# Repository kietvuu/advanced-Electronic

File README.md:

# advanced-Electronic
this is our project about H-bridge connection controlling a DC motor

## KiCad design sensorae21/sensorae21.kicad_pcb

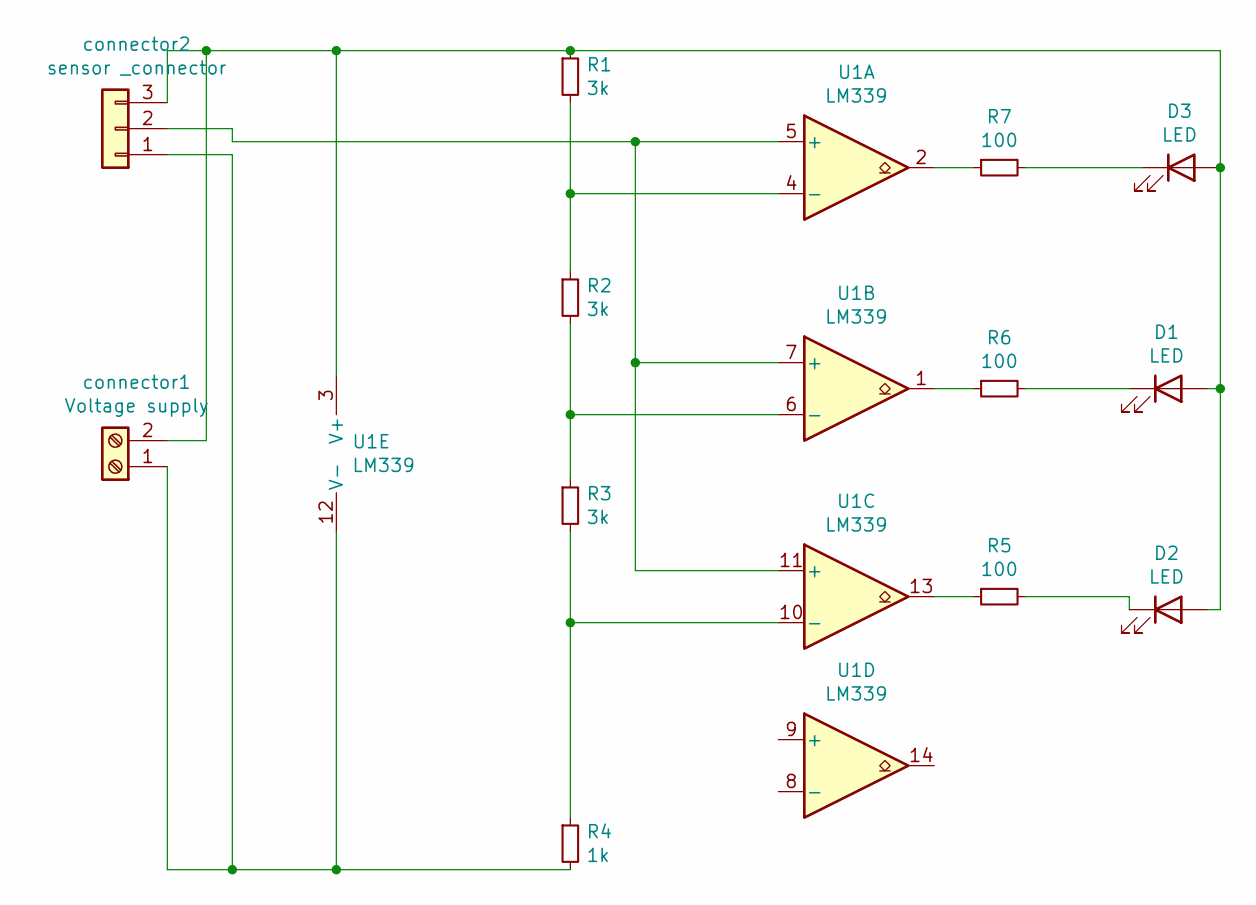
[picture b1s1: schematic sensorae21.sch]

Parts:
D1, D2, D3: LED; LED_D5.0mm
R1, R2, R3: 3k; R_Axial_DIN0309_L9.0mm_D3.2mm_P5.08mm_Vertical
R4: 1k; R_Axial_DIN0309_L9.0mm_D3.2mm_P5.08mm_Vertical
R5, R6, R7: 100; R_Axial_DIN0309_L9.0mm_D3.2mm_P5.08mm_Vertical
U1: LM339; DIP-14_W7.62mm
connector1: Voltage supply; PinSocket_1x02_P2.54mm_Vertical
connector2: sensor _connector; PinHeader_1x03_P2.54mm_Vertical

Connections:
unnamed: D1.1 (K), R6.2
unnamed: D1.2 (A), D2.2 (A), D3.2 (A), R1.1, U1.3 (V+), connector1.2, connector2.3
unnamed: D2.1 (K), R5.2
unnamed: D3.1 (K), R7.2
unnamed: R1.2, R2.1, U1.4 (-)
unnamed: R2.2, R3.1, U1.6 (-)
unnamed: R3.2, R4.1, U1.10 (-)
unnamed: R4.2, U1.12 (V-), connector1.1, connector2.1
unnamed: R5.1, U1.13
unnamed: R6.1, U1.1
unnamed: R7.1, U1.2
unnamed: U1.5 (+), U1.7 (+), U1.11 (+), connector2.2

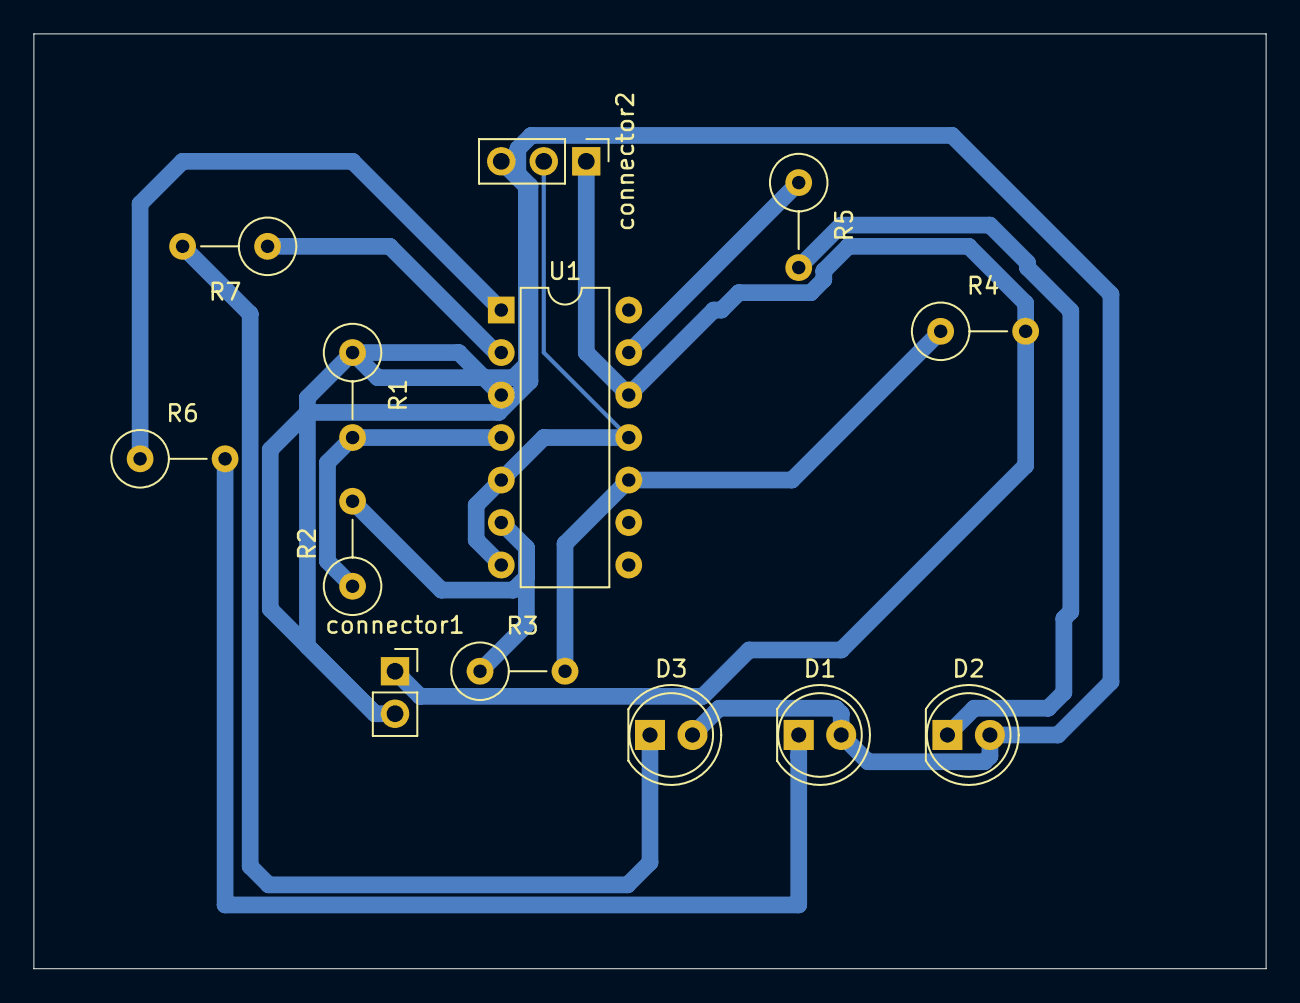
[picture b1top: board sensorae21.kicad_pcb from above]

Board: 2 copper layers, 73.7 x 55.9 mm, 13 parts (0 on the bottom side), 12 nets.

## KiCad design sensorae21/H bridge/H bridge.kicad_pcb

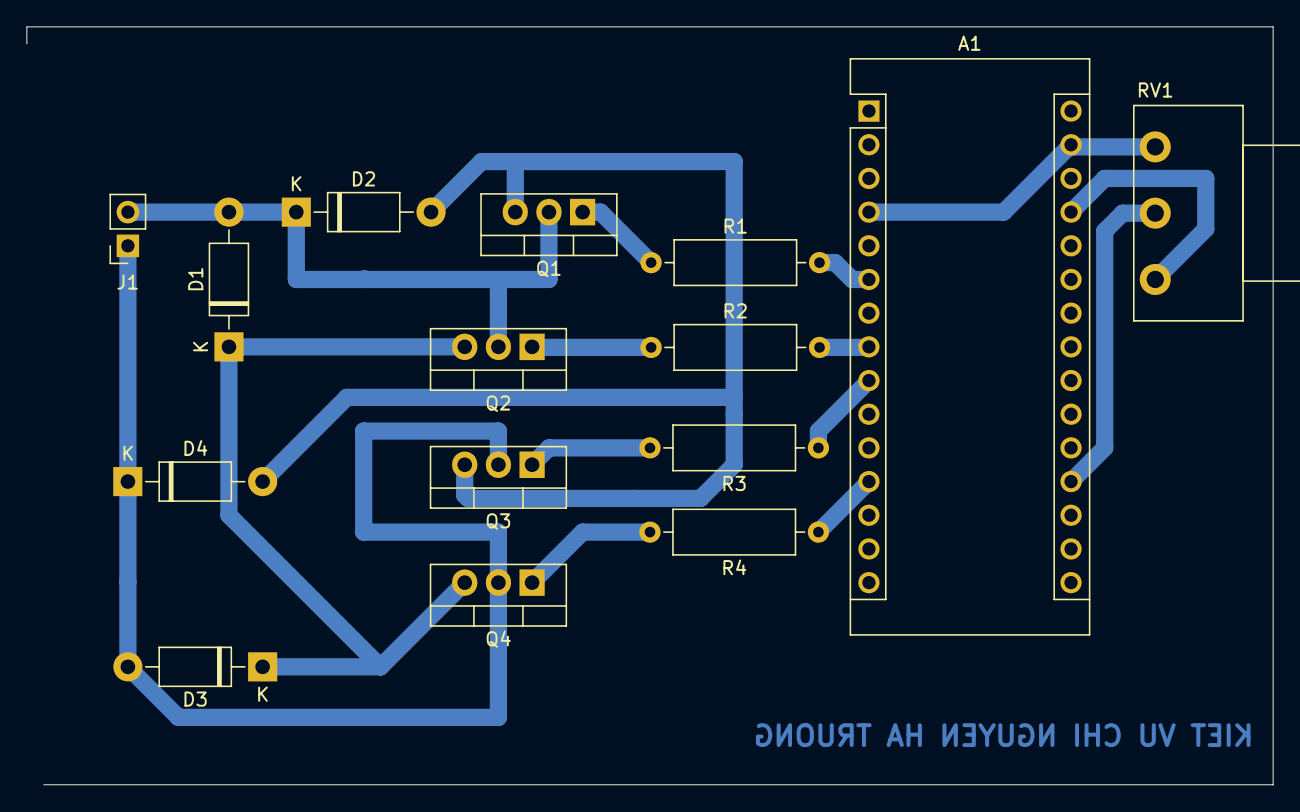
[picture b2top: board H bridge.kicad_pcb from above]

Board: 2 copper layers, 94.0 x 57.1 mm, 15 parts (0 on the bottom side), 15 nets.

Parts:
A1: Arduino_Nano_Every; Arduino_Nano
D1, D2, D3, D4: 1N4001; D_DO-41_SOD81_P10.16mm_Horizontal
J1: Screw_Terminal_01x02; PinSocket_1x02_P2.54mm_Vertical
Q1, Q3: TIP122; TO-220-3_Vertical
Q2, Q4: TIP127; TO-220-3_Vertical
R1, R2, R3, R4: R; R_Axial_DIN0309_L9.0mm_D3.2mm_P12.70mm_Horizontal
RV1: R_POT; Potentiometer_Piher_PC-16_Single_Horizontal

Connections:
GND: D2.2, D4.2, Q1.3, Q3.3
unnamed: A1.6, R1.2
unnamed: A1.8, R2.2
unnamed: A1.9, R3.1
unnamed: A1.12, R4.1
unnamed: A1.19, RV1.2
unnamed: A1.27, RV1.1
unnamed: A1.4, A1.29, RV1.3
unnamed: D1.1, D3.1, Q2.3, Q4.3
unnamed: D1.2, D2.1, J1.2, Q1.2, Q2.2
unnamed: D3.2, D4.1, J1.1, Q3.2, Q4.2
unnamed: Q1.1, R1.1
unnamed: Q2.1, R2.1
unnamed: Q3.1, R3.2
unnamed: Q4.1, R4.2
